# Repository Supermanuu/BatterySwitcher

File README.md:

# Sofle Battery Switcher

We are triying to make a battery switch for the Sofle Keyboard, or properly said, the [nRFMicro](https://github.com/joric/nrfmicro/tree/1.4) or Pro Micro compatible board used by the [Sofle](https://github.com/josefadamcik/SofleKeyboard) Keyboard.

Our goal is to have a PCB that could short and open the baterry supply via a switch, keeping as low profile as possible and doing it as integrated as possible. Also, the device should change the battery in any of the positions, because the `nRFMicro` has a battery charge monitor.

## Setup

In order to use this repo you should add a `KICAD_3RD_PARTY` variable with `${KIPRJMOD}/3rdparty/` value. If you had installed Kicad for all users, the variable shall be a system variable. Otherwise it can be a user variable.

Also, to commit the messages we use <https://github.com/marketplace/actions/github-actions-create-tag>, so your commit messages need to follow a certain format. In order to do so, you need to install some git hooks. You can do that by running the following command:

```bash
./scripts/setup-hooks.sh
```

## Used plugins

* For download parts from [Component Search Engine](https://componentsearchengine.com/): [Import-LIB-KiCad-Plugin](https://github.com/Steffen-W/Import-LIB-KiCad-Plugin)

## Documentation

See [the documentation](doc/user-guide.md).

## Releases

See [Github releases](https://github.com/Supermanuu/BatterySwitcher/releases).

Each release has:

* User guide in `user-guide.html`, with a lot of information to build the PCB.
* iBOM in `ibom.html`, with all the PCB parts.
* Another BOM in `out-of-bom.html`, with parts not used by the PCB, but needed in some cases.
* Schematic in `schematic.pdf`, with the diagram of the PCB.
* PCB images:
  * top view in `top.png`.
  * bottom view in `bottom.png`.

Another attach has:

* Gerber files and drill files in `manufacturing.zip`
* 3D model in `3D.step`

## Generate release

To generate a release you will need to create a new `release/*` branch and make a PR from that branch to main. In that scenario, when the PR is closed a job will be launched. That job will generate a tag and a release with all the change information from the previous tag until now, using the commit contents as specified in <https://github.com/marketplace/actions/github-tag>.

### Release changelog management

In order to auto-generate the changelog, the commits shall use this rules:

| Keyword           | Example                                                            | Increases |
|-------------------|--------------------------------------------------------------------|-----------|
| `fix(something)`  | fix(pencil): stop graphite breaking when too much pressure applied | Patch     |
| `feat(something)` | feat(pencil): add 'graphiteWidth' option                           | Minor     |
| `perf(something)` | perf(pencil): remove graphiteWidth option                          | Major     |

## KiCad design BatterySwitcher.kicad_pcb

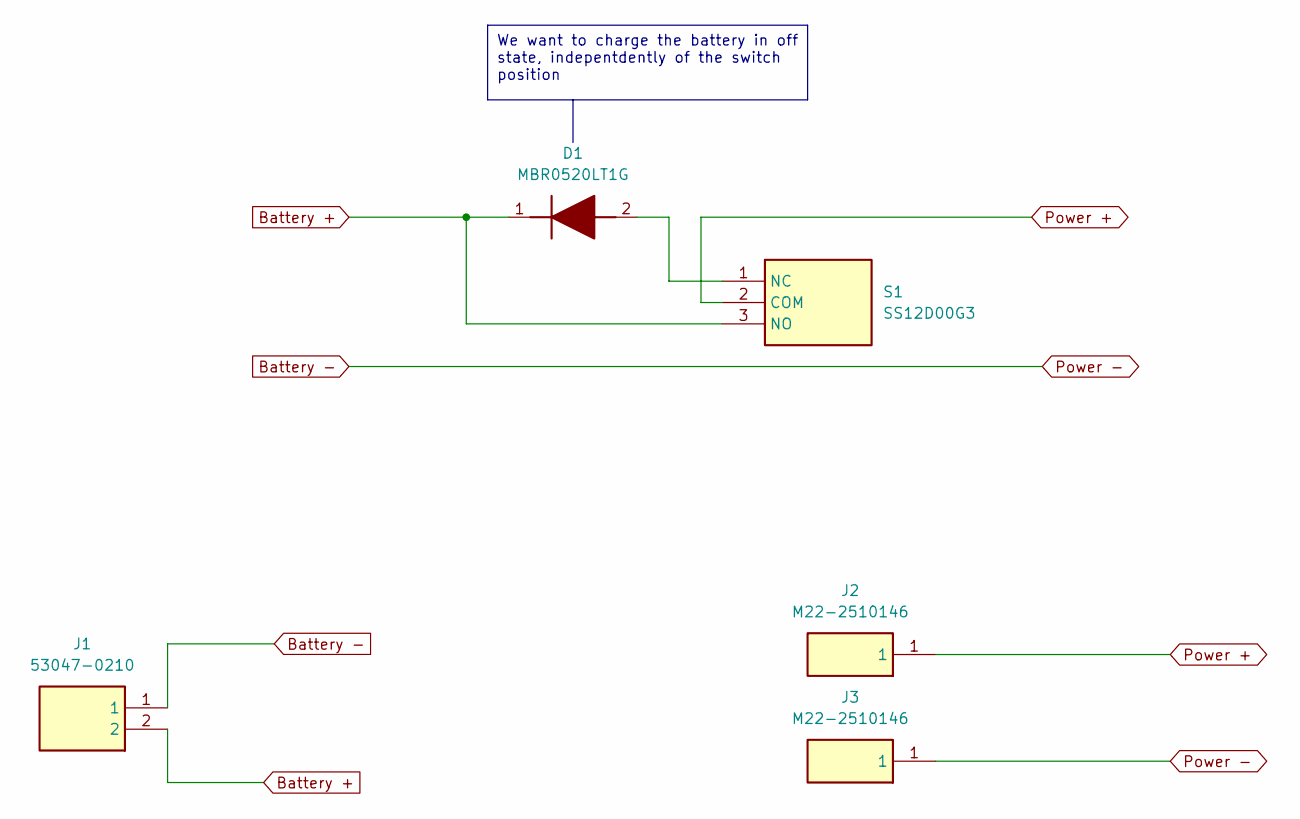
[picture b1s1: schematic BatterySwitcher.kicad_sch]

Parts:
D1: MBR0520LT1G; SOD3716X135N; Manufacturer_Part_Number MBR0520LT1G; Mouser Part Number 863-MBR0520LT1G
J1: 53047-0210; 530470210; Manufacturer_Part_Number 53047-0210; Mouser Part Number 538-53047-0210
J2, J3: M22-2510146; HDRV1W50P0X200_1X1_200X200X525P; Manufacturer_Part_Number M22-2510146; Mouser Part Number 855-M22-2510146
S1: SS12D00G3; Manufacturer_Part_Number SS12D00G3

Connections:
Battery +: D1.1 (K), J1.2, S1.3 (NO)
Battery -: J1.1, J3.1
unnamed: D1.2 (A), S1.1 (NC)
Power +: J2.1, S1.2 (COM)

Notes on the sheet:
We want to charge the battery in off state, indepentdently of the switch position

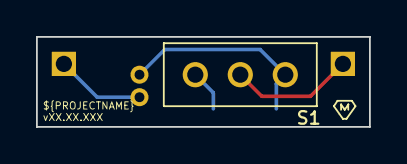
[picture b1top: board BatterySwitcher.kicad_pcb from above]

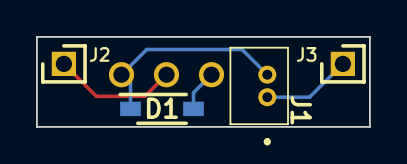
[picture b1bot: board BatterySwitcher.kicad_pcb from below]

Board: 2 copper layers, 18.5 x 5.0 mm, 5 parts (4 on the bottom side), 4 nets.

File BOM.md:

#  Bill of materials

## From PCB

| Reference | Qty | Value            | Datasheet                                                                                        | Footprint                   |
|---        |---  |---               |---                                                                                               |---                          |
|  D1       | 1   | CUHS20S30,H3F    | https://www.mouser.es/ProductDetail/Toshiba/CUHS20S30H3F?qs=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     | SamacSys_Parts:CUHS20S40H3F |
|  J1       | 1   | Battery          | https://www.mouser.es/ProductDetail/Molex/53047-0210?qs=M5Ic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         | SamacSys_Parts:530470210    |
|  J2       | 1   | Power +          | ~                                                             | Connector_PinHeader_1.00mm:PinHeader_1x01_P1.00mm_Vertical     |
|  J3       | 1   | Power -          | ~                                                             | Connector_PinHeader_1.00mm:PinHeader_1x01_P1.00mm_Vertical     |
|  S1       | 1   | SLW-883935-2A-D  | https://www.mouser.es/ProductDetail/179-SLW-883935-2A-D                                          | SLW8839352AD                |

## Not from PCB

| Reference  | Qty | Datasheet                                                                              | Purpouse                 |
|---         |---  |---                                                                                     |---                       |
| 51021-0200 | 1   | https://www.mouser.es/ProductDetail/Molex/51021-0200?qs=pAYF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 | Battery cable connection |
| 50079-8001 | 2   | https://www.mouser.es/ProductDetail/Molex/50079-8001?qs=rQFj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 | Battery cable connection |

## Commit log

2024-05-19 only dip pins left
2024-05-19 removed unused files
2024-05-19 using official gitignore
2024-05-19 added dip pins for battery and power connections and routing done
2024-05-20 acciones de la revision de la placa
2024-05-20 fixed some issues noticed from Miguel Angel
    Removed ground plane
    Checked copper width for 500mA
    Changed diode to shottky with less forward voltage
    Added battery connector
    Rearrange header pins to be from behind
    Reroute all
2024-05-21 real spacing requirements
2024-05-21 changed switch by a shorter one
    achieved minimum footprint
2024-05-21 added todos
2024-05-21 added 3rd party symbols
2024-05-22 using 3rd party from repo
2024-05-22 fixed header pins polarity
2024-05-27 fixed J3 silkscreen cut
2024-05-27 changed arrange to 5mm
2024-05-27 added readme and changed severity of courtyards_overlap
2024-05-27 tuning pipeline outputs
2024-05-27 temporally disable drc
2024-05-28 Actualizar gerber.yml
2024-05-28 fixed gerber.yml
2024-05-31 removed normal bom
2024-05-31 markdown documentation and new components
2024-05-31 finished development
2024-05-31 added documentation and user manual
2024-05-31 fixed release typo
2024-05-31 fixed repeated name in pick and place file
2024-05-31 fixed 2 drc silkscreen
2024-05-31 try to fix cp command
2024-05-31 using coimppose before
2024-05-31 fixed otheer typo
2024-05-31 fine tuning
2024-06-19 Added 3d generation
2024-06-19 add 3d artifact
2024-06-19 fixed missing path parameter
2024-06-23 added important comment over system variables
2024-06-23 fixed bad headers
    Now headers are 0.5 square
    PCB size increased in 1mm length, wide remains the same
    Rotated J1 due spacing
    Rerouted PCB
2024-06-23 new idea: put behind hte battery connector
2024-06-23 todo
2024-06-25 added KICAD_3RD_PARTY environment variable
2024-06-25 removed consolas font
2024-06-25 added directory inspection
2024-07-05 added real board
2024-07-05 added sofle keyboard url
2024-07-31 removed todo
2024-07-31 added git version
2024-07-31 this is not working on actions
2024-07-31 enabled kibot from terminal
2024-07-31 fixed git version in gihub
    the docker cannot use the /data direcotry because it was not safe
2024-07-31 added dirty flag
2024-07-31 Revert "added dirty flag"
    This reverts commit 7186b8e69e2a3c01888ff5795c45114670019ff5.
2024-07-31 improved version replacement placeholder
2024-07-31 fixed J2 and J3 placement
2024-07-31 added git version gathering error checking
2024-07-31 renamed actions file and added git tag fetch
2024-07-31 improved again the version service
2024-07-31 fixed badge
2024-08-01 fixed user guide link in markdown
2024-08-02 added JLCPCB design requierements
2024-08-02 changed battery connector to be placed on the back
2024-08-02 fixed some docs
2024-08-02 added release branch versioning
2024-08-02 added shematic git versioning
2024-08-02 updated TODOs
2024-08-04 working on auto release
2024-08-09 feat(pencil): added semantic versioning
    fixed line endings and improved setup script
2024-08-09 fix(pencil): remove unnecessary branch check
2024-08-09 fix(pencil): added write permissions
2024-08-09 fix(pencil): added release badge
2024-08-09 fix(pencil): removed pipeline permissions. Using GHA settings instead
2024-08-09 fix(pencil): added release artifacts
2024-08-09 fix(publish pipeline): renamed old release pipeline to publish pipeline
2024-08-09 fix(publish release): calling release generation from release publish. Removed release generation from main pushes
2024-08-09 fix(publish release): fixed calling pipeline not found
2024-08-09 fix(publish release): added release generation as previous dependant job
2024-08-09 fix(publish release): using mathieudutour/github-tag-action in release.yml
    Now the tag info is retrieved by a dry run of the mathieudutour/github-tag-action that not creates any tag in the end term
    The version placeholder has been shorten too
2024-08-09 fix(publish release): forgot to uncomment the `needs` definition
2024-08-09 fix(publish release): fized 3d-vX.X.X.zip upload fix(publish release): added main branch check before executing pipeline. This pipeline has to be executed only from main branch.
2024-08-09 fix(publish release): added missing 3D STEP extension
2024-08-09 fix(general): added license
2024-08-09 N/A: added not applicable change log into the version history
    This will be used for non versionable changes, like documentation, repo management changes... etc
2024-08-10 N/A: updated kibot and added drc check
2024-08-10 na: gather warnings and errors
2024-08-10 na: fixed bad yaml format
2024-08-10 na: redirecting error output to sed
2024-08-13 N/A: try out this kind of error and warning formatting
2024-08-13 N/A: forgot to add docker compose command in kibot launch
2024-08-13 N/A: try GHA warning bash output
2024-08-13 N/A: updated readme
2024-08-30 N/A: reviewed mounting manual
2024-08-30 feat(updated documentation): added detailed mounting manual
